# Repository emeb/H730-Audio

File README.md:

# H730-Audio

A small audio DSP board with GPIO, GUI and SD card.

## Abstract

A few years ago I was approached by my friend and colleague [Robert Rich](https://robertrich.com/) to help with a fascinating audio project that would be used to create immersive audio installations. He needed a device that would process sound in different ways - sometimes responding to sound, sometimes responding to environmental conditions. We kicked the ideas around for a while and tried various off-the-shelf solutions (Raspberry Pi, etc) but nothing was quite right so I ended up designing the H730 Audio board from scratch specifically for his requirements. The board needed audio input and output, storage, on-site configurability and the ability to use light sensors and this is what we ended up with:

- STM32H730 microcontroller - this is a compact, inexpensive and powerful device with plenty of I/O and on-chip resources that make for a capable "blank slate" on which to implement any DSP we might come up with

- WM8731 codec - I had a good stock of these in my inventory and I was very familiar with it. The device is EOL now and difficult to get, but in 2020 it was still a viable option. Today I'd probably use something like the Nuvoton NAU88C22 for equivalent features and performance.

- Micro SD-card slot - this is for storing long audio files of ambient recording and playback.

- 8 channel voltage-protected GPIO on a terminal block - for connecting sensors in environmental response installations. Specifically we used surplus solar panels to detect light changes throughout the day in order to modulate audio pitch and timbre.

- Micro USB - primarily used for 5V power, but also for USB DFU software updates.

- 240x240 IPS LCD - for user interface.

- Rotary encoder with pushbutton - for user interface.

- Quad SPI footprint for PSRAM or Flash memory - for audio sample storage or delay memory.

- 32kB I2C EEPROM - for user setting storage.

- Miscellaneous I/O headers for debug/development and "future expansion"

## Hardware

The design was created in an older version of Kicad and five boards were hand assembled - four went to Robert and several have been used in museum installations along with supporting hardware hand-built by Robert. The remaining board is in my collection. Design materials can be found in the [Hardware](./Hardware) directory.

## Firmware

Applications for this board were created in C using the STM32 HAL and ARM CMSIS libraries. Two audio installations are supported - a light-sensitive cloud generator and a day-long audio environment delay/feedback system. The source code for these applications is not provided at this time as they are proprietary, but basic hardware drivers are available in the [Firmware](./Firmware) directory.

## Documentation

The full users guide for the board with info on the I/O ports and use of the audio applications is here: [User Guide](./doc/h730_audio_info.pdf)

The board schematic is here: [Schematic](./doc/h730_audio_sch.pdf)

## Going Further

 Robert has a nice write-up on the system this board was used in over on his site that includes photos and videos:

[Sound Sculpture](https://robertrich.com/graphic-art/sound-sculpture/)

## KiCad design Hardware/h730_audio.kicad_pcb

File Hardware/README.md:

## H730 Audio - Hardware

This directory contains the Kicad 9.x design data for the H730 Audio board.
Note this was originally created in an earlier version of Kicad and although
was functional and correct in that environment, it has been automatically
upgraded to 9.x so there may be errors. Please use caution, run all applicable
DRC checks, etc before attempting to fab this design.

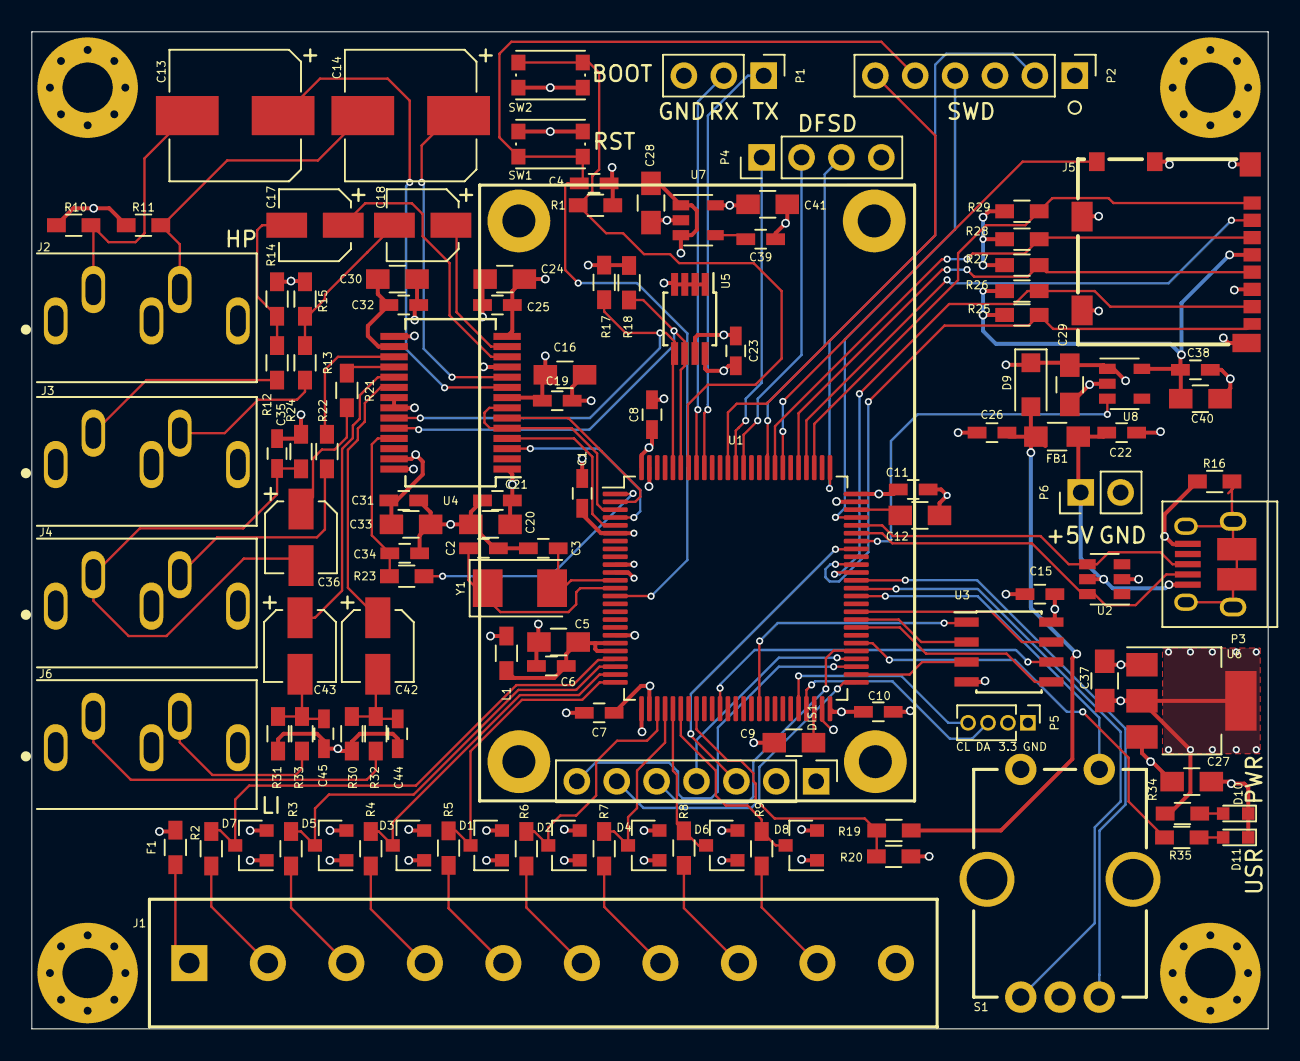
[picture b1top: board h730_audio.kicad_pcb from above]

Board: 4 copper layers, 78.7 x 63.5 mm, 123 parts (0 on the bottom side), 101 nets.

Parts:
C1, C4, C6, C7, C8, C10, C11, C15, C19, C21, C23, C25, C31, C32, C38, C39: 0.1uf; C_0603_HandSoldering
C2, C3: 33pf; C_0603_HandSoldering
C5, C16, C20, C24, C27, C28, C29, C30, C33, C37, C40, C41: 10uf; C_0805_HandSoldering
C9, C12: 2.2uf; C_0805_HandSoldering
C13, C14: 220uF; CP_Elec_8x10.5
C17, C18: 10uF; CP_Elec_4x5.3
C22, C26, C34, C35, C44, C45: 220pf; C_0603_HandSoldering
C36, C42, C43: 1uF; CP_Elec_4x5.3
D1, D2, D3, D4, D5, D6, D7, D8: BAT54S; SOT-23
D9: D_Schottky; D_SOD-123W
D10, D11: LED; LED_0603
DIS1: IPS_LCD
F1: Polyfuse; R_0603_HandSoldering
FB1: Ferrite_Bead; R_0805_HandSoldering
H1, H2, H3, H4: MountingHole; MountingHole_3.2mm_M3_Pad_Via
J1: Screw_Terminal_01x10; screw_terminal_10
J2, J3, J4, J6: STEREO_JACK; CUI_SJ1-3535NG-GR
J5: Micro_SD_Card_Det; micro_sd_molex_1040310-811
L1: 1k; R_0603_HandSoldering
P1: CONN_01X03; Pin_Header_Straight_1x03_Pitch2.54mm
P2: CONN_01X06; Pin_Header_Straight_1x06_Pitch2.54mm
P3: USB_OTG; USB_Micro-B_10103594-0001LF
P4: CONN_01X03; Pin_Header_Straight_1x04_Pitch2.54mm
P5: CONN_01X04; Pin_Header_Straight_1x04_Pitch1.27mm
P6: CONN_01X03; Pin_Header_Straight_1x02_Pitch2.54mm
R1, R17, R18, R19, R20: 4.7k; R_0603_HandSoldering
R2, R3, R4, R5, R6, R7, R8, R9, R12, R13: 100; R_0603_HandSoldering
R10, R11, R14, R15, R24: 47k; R_0603_HandSoldering
R16: 1M; R_0603_HandSoldering
R21, R25, R26, R27, R28, R29: 10k; R_0603_HandSoldering
R22: 680; R_0603_HandSoldering
R23: 56; R_0603_HandSoldering
R30, R31, R32, R33: 5.6k; R_0603_HandSoldering
R34, R35: 1k; R_0603_HandSoldering
S1: encoder_en11; ENC_11
SW1, SW2: SW_PUSH; SW_SPST_KMR2
U1: STM32H730VBTx; LQFP-100_14x14mm_P0.5mm
U2: IP4220CZ6; SOT-23-6
U3: W25Q32JVSS; SOIC-8_3.9x4.9mm_Pitch1.27mm
U4: WM8731; SSOP-28_5.3x10.2mm_Pitch0.65mm
U5: 24LC256; MSOP-8_3x3mm_Pitch0.65mm
U6: LD1117S33TR_SOT223; SOT-223-3_TabPin2
U7: LP2985-3.3; SOT-23-5
U8: MCP1802x-xx02xOT; SOT-23-5
Y1: 8MHz; Crystal_SMD_Abracon_ABM3-2pin_5.0x3.2mm

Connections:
+3.3VA: C16.1, C19.1, C24.1, C25.1, C41.1, U4.8, U4.14, U7.5
+3V3: C1.1, C7.1, C8.1, C10.1, C11.1, C15.1, C20.1, C21.1, C23.1, C31.1, C33.1, C37.1, D1.2, D2.2, D3.2, D4.2, D5.2, D6.2, D7.2, D8.2, DIS1.2, F1.1, L1.1, P2.1, P5.2, R17.1, R18.1, R34.1, SW2.2, U1.6, U1.11, U1.27, U1.50, U1.75, U1.100, U3.8, U4.1, U4.27, U5.8, U6.2
/+3.3V_SD: C38.2, C40.1, J5.4, R25.1, R26.1, R27.1, R28.1, R29.1, U8.5
/BOOT: R1.1, SW2.1, U1.94
/DFSDM_C1: P4.1, U1.88
/DFSDM_CKO: P4.3, U1.84
/DFSDM_D1: P4.2, U1.87
/I2C2_SCL: P5.4, U1.46
/I2C2_SDA: P5.3, U1.47
/I2C_SCL: R18.2, U1.95, U4.24, U5.6
/I2C_SDA: R17.2, U1.96, U4.23, U5.5
/LCD_BL: DIS1.7, U1.53
/LCD_DC: DIS1.6, U1.51
/LCD_RES: DIS1.5, U1.55
/NRST: C4.1, P2.5, SW1.2, U1.14
/OCTSPIM_P1_CLK: U1.36, U3.6
/OCTSPIM_P1_IO0: U1.58, U3.5
/OCTSPIM_P1_IO1: U1.59, U3.2
/OCTSPIM_P1_IO2: U1.52, U3.3
/OCTSPIM_P1_IO3: U1.60, U3.7
/OCTSPIM_P1_NCS: U1.41, U3.1
/PA0: D7.3, R2.1, U1.22
/PA1: D5.3, R3.1, U1.23
/PA2: D3.3, R4.1, U1.24
/PA3: D1.3, R5.1, U1.25
/PA4: D2.3, R6.1, U1.28
/PA5: D4.3, R7.1, U1.29
/PA6: D6.3, R8.1, U1.30
/PA7: D8.3, R9.1, U1.31
/SAI_FS: U1.3, U4.5, U4.7
/SAI_MCLK: R23.1, U1.1
/SAI_SCK: U1.4, U4.3
/SAI_SD_A: U1.5, U4.4
/SAI_SD_B: U1.2, U4.6
/SD_CLK: J5.5, R27.2, U1.80
/SD_CMD: J5.3, R28.2, U1.83
/SD_D0: J5.7, R26.2, U1.65
/SD_D1: J5.8, R25.2, U1.66
/SD_D2: J5.1, R29.2, U1.78
/SD_D3: J5.2, U1.79
/SD_DET: J5.10, U1.82
/SD_PWR: U1.69, U8.3
/SPI2_MOSI: DIS1.4, U1.54
/SPI2_SCK: DIS1.3, U1.68
/SWD_DIO: P2.4, U1.72
/SWD_SWCLK: P2.2, U1.76
/SWD_SWO: P2.6, U1.89
/USART1_RX: P1.2, U1.93
/USART1_TX: P1.1, U1.92
/USB_DM: P3.2, U1.70, U2.6
/USB_DP: P3.3, U1.71, U2.4
/USR_LED: R35.1, U1.56
/VBUS: C22.1, FB1.2, P3.1, P6.1, U2.5
/VBUS_FILT: C26.1, D9.2, FB1.1, R19.1
/VBUS_Sense: R19.2, R20.1, U1.33
/VSUPPLY: C27.1, C28.1, C29.1, D9.1, U6.3, U7.1, U7.3, U8.1
/Vmid: C30.1, C32.1, U4.16
/Vref: C5.1, C6.1, L1.2, U1.20, U1.21
GND: C1.2, C2.2, C3.2, C4.2, C5.2, C6.2, C7.2, C8.2, C9.2, C10.2, C11.2, C12.2, C15.2, C16.2, C19.2, C20.2, C21.2, C22.2, C23.2, C24.2, C25.2, C26.2, C27.2, C28.2, C29.2, C30.2, C31.2, C32.2, C33.2, C34.2, C35.2, C37.2, C38.1, C39.2, C40.2, C41.2, C44.2, C45.2, D1.1, D2.1, D3.1, D4.1, D5.1, D6.1, D7.1, D8.1, D10.1, D11.1, DIS1.1, J1.10, J2.1, J3.1, J4.1, J4.4, J5.6, J5.9, J5.11, J6.1, J6.4, J6.5, P1.3, P2.3, P3.5, P4.4, P5.1, P6.2, R1.2, R10.2, R11.2, R14.2, R15.2, R16.1, R20.2, R24.1, R30.1, R31.1, S1.3, S1.4, SW1.1, U1.10, U1.19, U1.26, U1.49, U1.74, U1.99, U2.2, U3.4, U4.11, U4.15, U4.21, U4.22, U4.28, U5.1, U5.2, U5.3, U5.4, U5.7, U6.1, U7.2, U8.2
unnamed: C2.1, U1.13, Y1.1
unnamed: C3.1, U1.12, Y1.2
unnamed: C9.1, U1.48
unnamed: C12.1, U1.73
unnamed: C13.1, U4.9
unnamed: C13.2, J2.2, R10.1
unnamed: C14.1, U4.10
unnamed: C14.2, J2.3, R11.1
unnamed: C17.1, U4.12
unnamed: C17.2, R12.1, R14.1
unnamed: C18.1, U4.13
unnamed: C18.2, R13.1, R15.1
unnamed: C34.1, R23.2, U4.25
unnamed: C35.1, C36.2, J4.2, R24.2
unnamed: C36.1, R21.2
unnamed: C39.1, U7.4
unnamed: C42.1, U4.20
unnamed: C42.2, C44.1, R30.2, R32.1
unnamed: C43.1, U4.19
unnamed: C43.2, C45.1, R31.2, R33.1
unnamed: D10.2, R34.2
unnamed: D11.2, R35.2
unnamed: F1.2, J1.1
unnamed: J1.2, R2.2
unnamed: J1.3, R3.2
unnamed: J1.4, R4.2
unnamed: J1.5, R5.2
unnamed: J1.6, R6.2
unnamed: J1.7, R7.2
unnamed: J1.8, R8.2
unnamed: J1.9, R9.2
unnamed: J3.2, R12.2
unnamed: J3.3, R13.2
unnamed: J4.3, R22.2
unnamed: J6.2, R32.2
unnamed: J6.3, R33.2
unnamed: P3.6, R16.2
unnamed: R21.1, U4.18
unnamed: R22.1, U4.17
unnamed: S1.1, U1.63
unnamed: S1.2, U1.64
unnamed: S1.5, U1.62

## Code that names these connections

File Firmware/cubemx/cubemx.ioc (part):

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Mcu.Name=STM32H730VBTx
Mcu.Package=LQFP100
Mcu.UserName=STM32H730VBTx
PA0.Mode=IN16-Single-Ended
PA0.Signal=ADC1_INP16
PA1.Mode=IN17-Single-Ended
PA1.Signal=ADC1_INP17
PA11.Mode=Device_Only_FS
PA11.Signal=USB_OTG_HS_DM
PA12.Mode=Device_Only_FS
PA12.Signal=USB_OTG_HS_DP
PA13(JTMS/SWDIO).Mode=Trace_Asynchronous_SW
PA13(JTMS/SWDIO).Signal=DEBUG_JTMS-SWDIO
PA14(JTCK/SWCLK).Mode=Trace_Asynchronous_SW
PA14(JTCK/SWCLK).Signal=DEBUG_JTCK-SWCLK
PA2.Signal=ADCx_INP14
PA3.Signal=ADCx_INP15
PA4.Signal=ADCx_INP18
PA5.Signal=ADCx_INP19
PA6.Signal=ADCx_INP3
PA7.Signal=ADCx_INP7
PA9.Mode=Full_Duplex_Master
PA9.Signal=SPI2_SCK
PB10.Mode=I2C
PB10.Signal=I2C2_SCL
PB11.Mode=I2C
PB11.Signal=I2C2_SDA
PB13.Mode=OCTOSPI1_IOL_Port1L
PB13.Signal=OCTOSPIM_P1_IO2
PB14.Mode=Full_Duplex_Master
PB14.Signal=SPI2_MISO
PB15.Mode=Full_Duplex_Master
PB15.Signal=SPI2_MOSI
PB2.Mode=O1_P1_CLK
PB2.Signal=OCTOSPIM_P1_CLK
PB3(JTDO/TRACESWO).Mode=Trace_Asynchronous_SW
PB3(JTDO/TRACESWO).Signal=DEBUG_JTDO-SWO
PB6.Mode=Asynchronous
PB6.Signal=USART1_TX
PB7.Mode=Asynchronous
PB7.Signal=USART1_RX
PB8.Mode=I2C
PB8.Signal=I2C1_SCL
PB9.Mode=I2C
PB9.Signal=I2C1_SDA
PC10.Mode=SD_4_bits_Wide_bus
PC10.Signal=SDMMC1_D2
PC11.Mode=SD_4_bits_Wide_bus
PC11.Signal=SDMMC1_D3
PC12.Mode=SD_4_bits_Wide_bus
PC12.Signal=SDMMC1_CK
PC5.Signal=ADCx_INP8
PC8.Mode=SD_4_bits_Wide_bus
PC8.Signal=SDMMC1_D0
PC9.Mode=SD_4_bits_Wide_bus
PC9.Signal=SDMMC1_D1
PD11.Mode=OCTOSPI1_IOL_Port1L
PD11.Signal=OCTOSPIM_P1_IO0
PD12.Mode=OCTOSPI1_IOL_Port1L
PD12.Signal=OCTOSPIM_P1_IO1
PD13.Mode=OCTOSPI1_IOL_Port1L
PD13.Signal=OCTOSPIM_P1_IO3
PD2.Mode=SD_4_bits_Wide_bus
PD2.Signal=SDMMC1_CMD
PD3.Signal=S_CKOUTDFSDM1
PD6.Signal=S_DATAIN1DFSDM1
PD7.Signal=S_CKIN1DFSDM1
PE11.Mode=OCTOSPI1_Port1_NCS
PE11.Signal=OCTOSPIM_P1_NCS
PE2.Mode=SAI_A_MasterWithClock
PE2.Signal=SAI1_MCLK_A
PE3.Mode=SAI_B_SyncSlave
PE3.Signal=SAI1_SD_B
PE4.Mode=SAI_A_MasterWithClock
PE4.Signal=SAI1_FS_A
PE5.Mode=SAI_A_MasterWithClock
PE5.Signal=SAI1_SCK_A
PE6.Mode=SAI_A_MasterWithClock
PE6.Signal=SAI1_SD_A
PH0-OSC_IN.Mode=HSE-External-Oscillator
PH0-OSC_IN.Signal=RCC_OSC_IN
PH1-OSC_OUT.Mode=HSE-External-Oscillator
PH1-OSC_OUT.Signal=RCC_OSC_OUT
RCC.HSE_VALUE=8000000
RCC.SYSCLKFreq_VALUE=550000000
RCC.SYSCLKSource=RCC_SYSCLKSOURCE_PLLCLK
board=custom

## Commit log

2025-09-17 Initial commit of H730 Audio design materials and documentation
2025-11-27 Added link to Robert's page about this system

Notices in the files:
Hardware/h730_audio.kicad_pcb:
(c) 2021 E. Brombaugh
